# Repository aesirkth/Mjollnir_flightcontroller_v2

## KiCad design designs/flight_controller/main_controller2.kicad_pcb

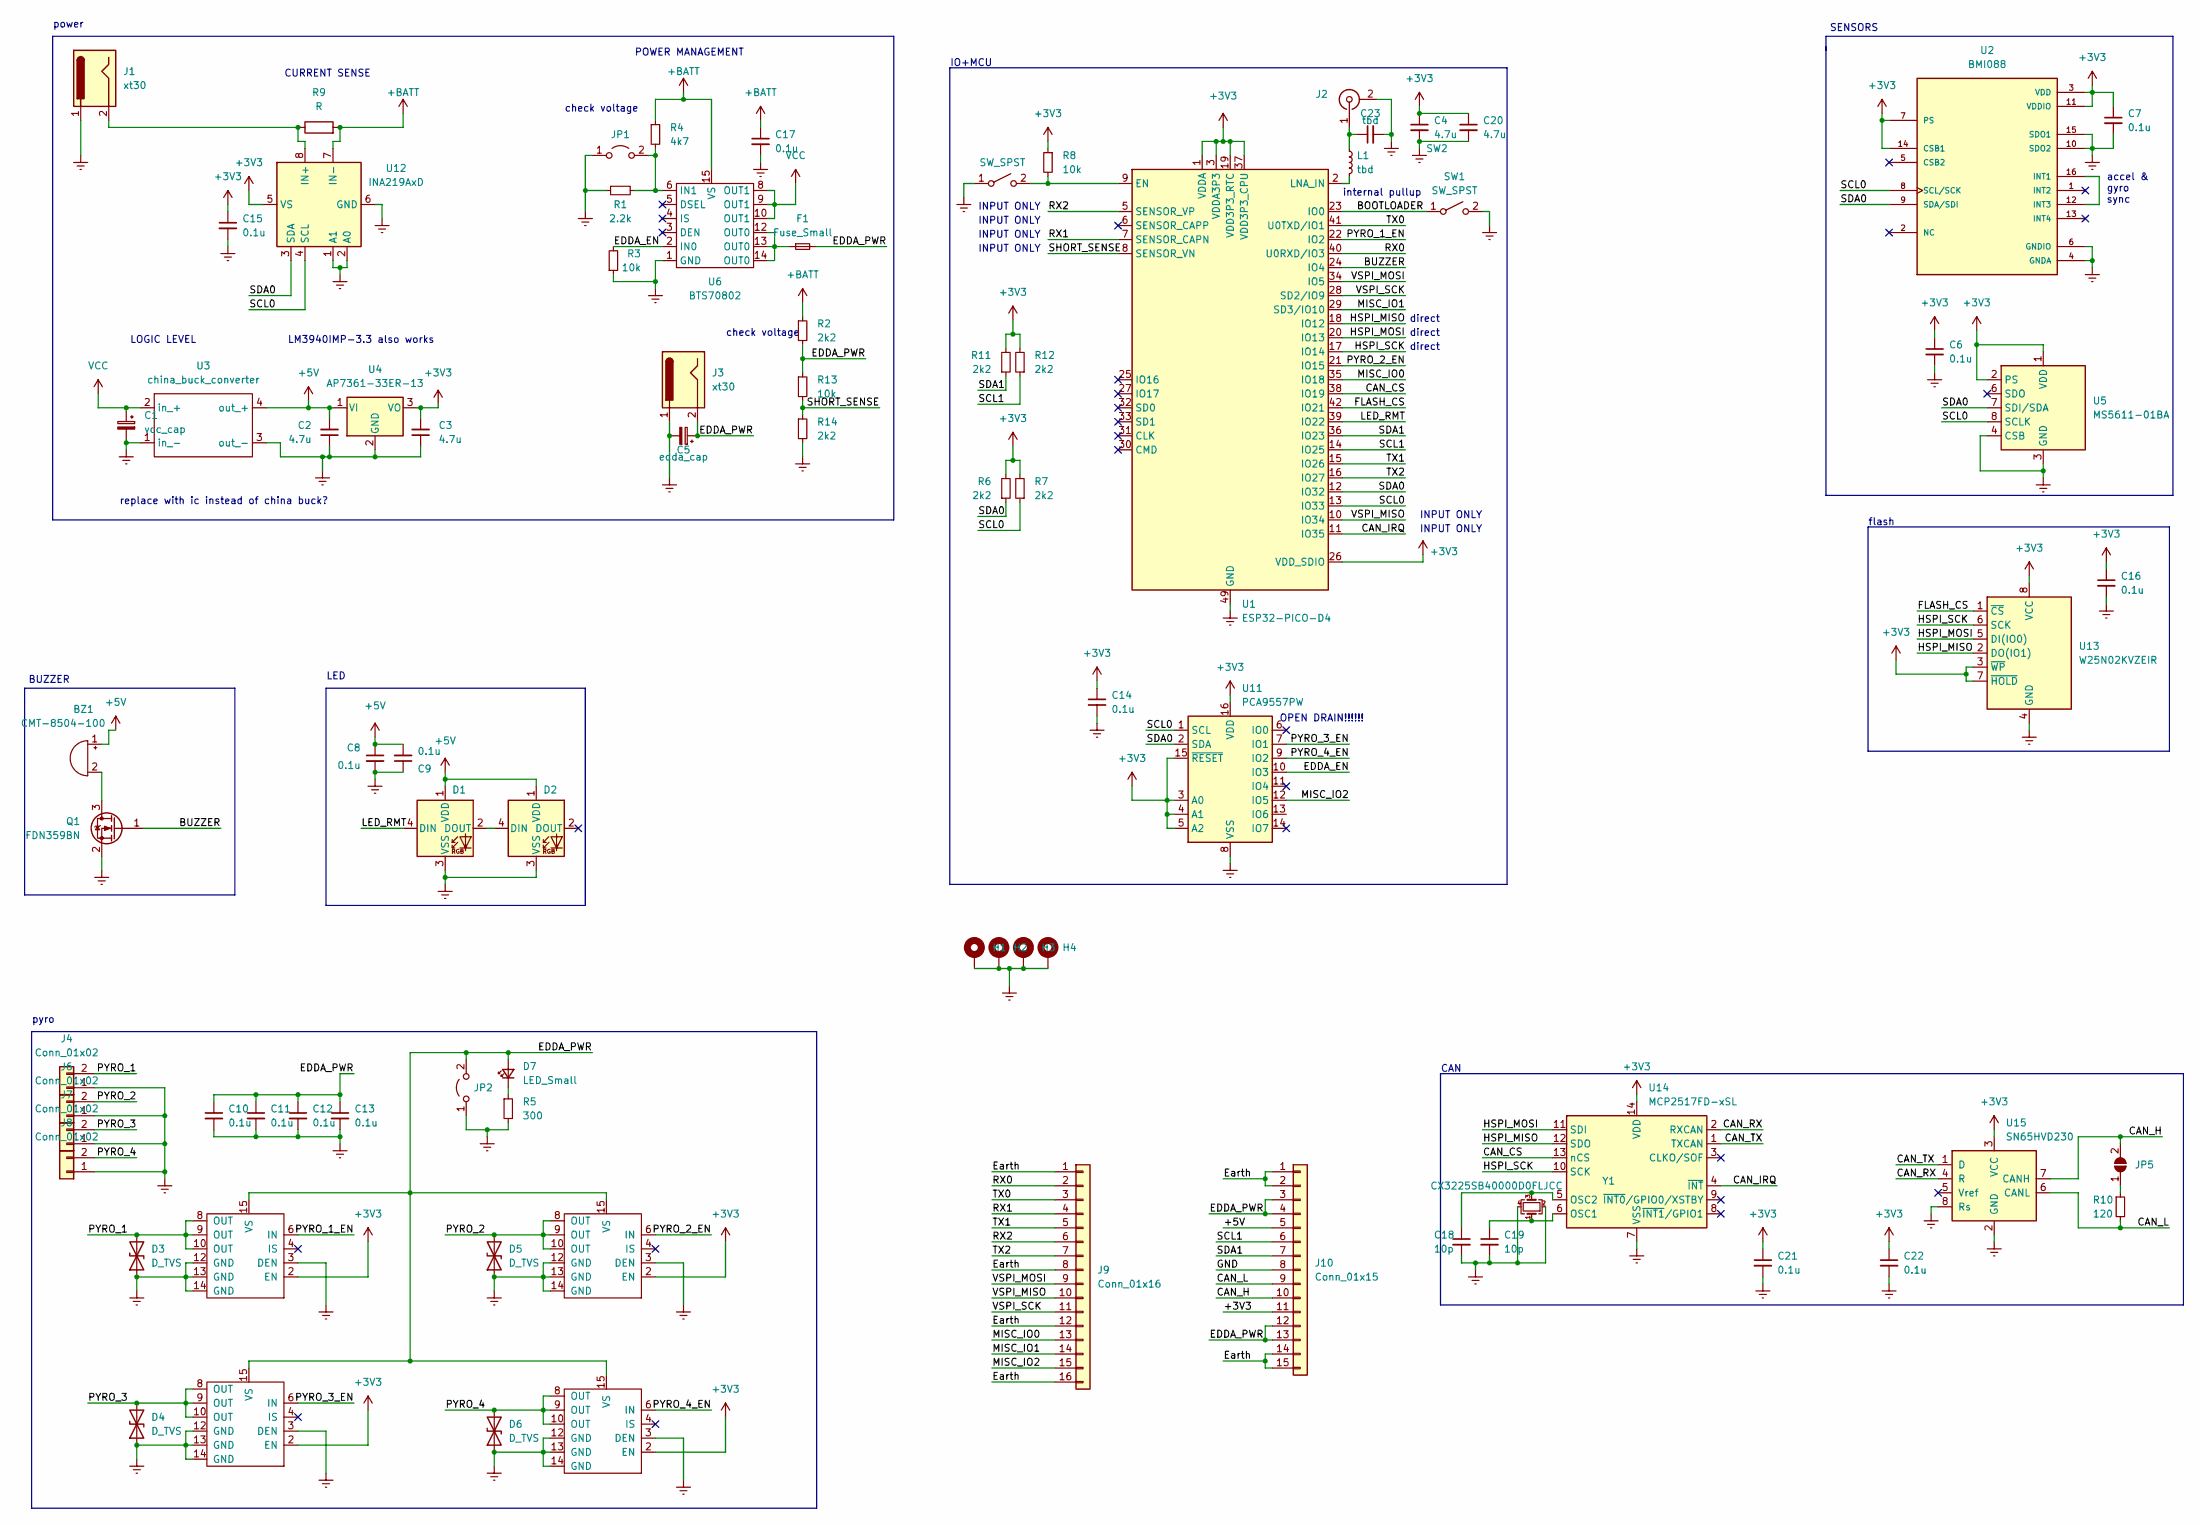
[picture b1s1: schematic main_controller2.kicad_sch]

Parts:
BZ1: CMT-8504-100; MagneticBuzzer_CUI_CMT-8504-100-SMT
C1: vcc_cap; CP_Radial_D5.0mm_P2.50mm
C2, C3, C4, C20: 4.7u; C_0603_1608Metric
C5: edda_cap; CP_Radial_D5.0mm_P2.50mm
C6, C7, C8, C9, C10, C11, C12, C13, C14, C15, C16, C17, C21, C22: 0.1u; C_0603_1608Metric
C18, C19: 10p; C_0603_1608Metric
C23: tbd; C_0603_1608Metric
D1, D2: WS2812B; LED_WS2812B_PLCC4_5.0x5.0mm_P3.2mm
D3, D4, D5, D6: D_TVS; D_0805_2012Metric
D7: LED_Small; D_0805_2012Metric
F1: Fuse_Small; Fuse_1812_4532Metric_Pad1.30x3.40mm_HandSolder
H1, H2, H3, H4: MountingHole_Pad; MountingHole_2.2mm_M2_Pad_Via
J1: xt30; AMASS_XT30PW-M_1x02_P2.50mm_Horizontal
J2: Conn_Coaxial; U.FL_Molex_MCRF_73412-0110_Vertical
J3: xt30; AMASS_XT30PW-F_1x02_P2.50mm_Horizontal
J4, J6, J7, J8: Conn_01x02; JST_XH_S2B-XH-A_1x02_P2.50mm_Horizontal
J9: Conn_01x16; PinHeader_1x16_P2.54mm_Vertical
J10: Conn_01x15; PinHeader_1x15_P2.54mm_Vertical
JP1: power switch; JST_XH_S2B-XH-A_1x02_P2.50mm_Horizontal
JP2: pyro_arm; AMASS_XT30PW-F_1x02_P2.50mm_Horizontal
JP5: SolderJumper_2_Open; SolderJumper-2_P1.3mm_Open_TrianglePad1.0x1.5mm
L1: tbd; L_0603_1608Metric
Q1: FDN359BN; SOT-23
R1: 2.2k; R_0603_1608Metric
R2, R6, R7, R11, R12, R14: 2k2; R_0603_1608Metric
R3, R8, R13: 10k; R_0603_1608Metric
R4: 4k7; R_0603_1608Metric
R5: 300; R_0603_1608Metric
R9: R; R_1206_3216Metric_Pad1.30x1.75mm_HandSolder
R10: 120; R_0603_1608Metric
SW1, SW2: SW_SPST; PinHeader_1x02_P1.27mm_Vertical
U1: ESP32-PICO-D4; QFN-48-1EP_7x7mm_P0.5mm_EP5.3x5.3mm
U2: BMI088; PQFN50P450X300X100-16N
U3: china_buck_converter; china_buck
U4: AP7361-33ER-13; SOT-223-3_TabPin2
U5: MS5611-01BA; LGA-8_3x5mm_P1.25mm
U6: BTS70802; Infineon_PG-TSDSO-14-22
U7, U8, U9, U10: BTN7030-1EPA; Infineon_PG-TSDSO-14-22
U11: PCA9557PW; TSSOP-16_4.4x5mm_P0.65mm
U12: INA219AxD; SOIC-8_3.9x4.9mm_P1.27mm
U13: W25N02KVZEIR; SON127P800X600X80-9N-D
U14: MCP2517FD-xSL; SOIC-14_3.9x8.7mm_P1.27mm
U15: SN65HVD230; SOIC-8_3.9x4.9mm_P1.27mm
Y1: CX3225SB40000D0FLJCC

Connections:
+3V3: C3.2, C4.1, C6.1, C7.1, C14.1, C15.1, C16.1, C20.1, C21.1, C22.1, J10.11, R6.2, R7.2, R8.1, R11.2, R12.2, U1.1 (VDDA), U1.3 (VDDA3P3), U1.4 (VDDA3P3), U1.19 (VDD3P3_RTC), U1.26 (VDD_SDIO), U1.37 (VDD3P3_CPU), U1.43 (VDDA), U1.46 (VDDA), U2.3 (VDD), U2.7 (PS), U2.11 (VDDIO), U2.14 (CSB1), U4.3 (VO), U5.1 (VDD), U5.2 (PS), U7.2 (EN), U8.2 (EN), U9.2 (EN), U10.2 (EN), U11.3 (A0), U11.4 (A1), U11.5 (A2), U11.15 (~RESET), U11.16 (VDD), U12.5 (VS), U13.3 (~WP), U13.7 (~HOLD), U13.8 (VCC), U14.14 (VDD), U15.3 (VCC)
+5V: BZ1.1 (-), C2.2, C8.1, C9.2, D1.1 (VDD), D2.1 (VDD), J10.5, U3.4 (out_+), U4.1 (VI)
+BATT: C17.1, R2.1, R4.1, R9.2, U6.15 (VS), U12.7 (IN-)
/BOOTLOADER: SW1.1 (A), U1.23 (IO0)
/BUZZER: Q1.1 (G), U1.24 (IO4)
/CAN_CS: U1.38 (IO19), U14.13 (nCS)
/CAN_H: J10.10, JP5.2 (B), U15.7 (CANH)
/CAN_IRQ: U1.11 (IO35), U14.4 (~INT)
/CAN_L: J10.9, R10.2, U15.6 (CANL)
/CAN_RX: U14.2 (RXCAN), U15.4 (R)
/CAN_TX: U14.1 (TXCAN), U15.1 (D)
/EDDA_EN: R3.2, U6.2 (IN0), U11.10 (IO3)
/EDDA_PWR: C5.1, C10.1, C11.1, C12.1, C13.1, D7.2 (A), F1.2, J3.2, J10.3, J10.4, J10.12, J10.13, JP2.2 (B), R2.2, R13.1, U7.15 (VS), U8.15 (VS), U9.15 (VS), U10.15 (VS)
/FLASH_CS: U1.42 (IO21), U13.1 (~CS)
/GND: J10.8
/HSPI_MISO: U1.18 (IO12), U13.2 (DO(IO1)), U14.12 (SDO)
/HSPI_MOSI: U1.20 (IO13), U13.5 (DI(IO0)), U14.11 (SDI)
/HSPI_SCK: U1.17 (IO14), U13.6 (SCK), U14.10 (SCK)
/LED_RMT: D1.4 (DIN), U1.39 (IO22)
/MISC_IO0: J9.13, U1.35 (IO18)
/MISC_IO1: J9.14, U1.29 (SD3/IO10)
/MISC_IO2: J9.15, U11.12 (IO5)
/PYRO_1: D3.2 (A2), J4.2, U7.8 (OUT), U7.9 (OUT), U7.10 (OUT)
/PYRO_1_EN: U1.22 (IO2), U7.6 (IN)
/PYRO_2: D5.2 (A2), J6.2, U9.8 (OUT), U9.9 (OUT), U9.10 (OUT)
/PYRO_2_EN: U1.21 (IO15), U9.6 (IN)
/PYRO_3: D4.2 (A2), J7.2, U8.8 (OUT), U8.9 (OUT), U8.10 (OUT)
/PYRO_3_EN: U8.6 (IN), U11.7 (IO1)
/PYRO_4: D6.2 (A2), J8.2, U10.8 (OUT), U10.9 (OUT), U10.10 (OUT)
/PYRO_4_EN: U10.6 (IN), U11.9 (IO2)
/RX0: J9.2, U1.40 (U0RXD/IO3)
/RX1: J9.4, U1.7 (SENSOR_CAPN)
/RX2: J9.6, U1.5 (SENSOR_VP)
/SCL0: R7.1, U1.13 (IO33), U2.8 (SCL/SCK), U5.8 (SCLK), U11.1 (SCL), U12.4 (SCL)
/SCL1: J10.6, R12.1, U1.14 (IO25)
/SDA0: R6.1, U1.12 (IO32), U2.9 (SDA/SDI), U5.7 (SDI/SDA), U11.2 (SDA), U12.3 (SDA)
/SDA1: J10.7, R11.1, U1.36 (IO23)
/SHORT_SENSE: R13.2, R14.1, U1.8 (SENSOR_VN)
/TX0: J9.3, U1.41 (U0TXD/IO1)
/TX1: J9.5, U1.15 (IO26)
/TX2: J9.7, U1.16 (IO27)
/VSPI_MISO: J9.10, U1.10 (IO34)
/VSPI_MOSI: J9.9, U1.34 (IO5)
/VSPI_SCK: J9.11, U1.28 (SD2/IO9)
Earth: C1.2, C2.1, C3.1, C4.2, C5.2, C6.2, C7.2, C8.2, C9.1, C10.2, C11.2, C12.2, C13.2, C14.2, C15.2, C16.2, C17.2, C18.2, C19.2, C20.2, C21.2, C22.2, C23.2, D1.3 (VSS), D2.3 (VSS), D3.1 (A1), D4.1 (A1), D5.1 (A1), D6.1 (A1), H1.1, H2.1, H3.1, H4.1, J1.1, J2.2 (Ext), J3.1, J4.1, J6.1, J7.1, J8.1, J9.1, J9.8, J9.12, J9.16, J10.1, J10.2, J10.14, J10.15, JP1.1 (A), JP2.1 (A), Q1.2 (S), R1.1, R3.1, R5.2, R14.2, SW1.2 (B), SW2.1 (A), U1.49 (GND), U2.4 (GNDA), U2.6 (GNDIO), U2.10 (SDO2), U2.15 (SDO1), U3.1 (in_-), U3.3 (out_-), U4.2 (GND), U5.3 (GND), U5.4 (CSB), U5.5 (CSB), U6.1 (GND), U7.3 (DEN), U7.12 (GND), U7.13 (GND), U7.14 (GND), U8.3 (DEN), U8.12 (GND), U8.13 (GND), U8.14 (GND), U9.3 (DEN), U9.12 (GND), U9.13 (GND), U9.14 (GND), U10.3 (DEN), U10.12 (GND), U10.13 (GND), U10.14 (GND), U11.8 (VSS), U12.1 (A1), U12.2 (A0), U12.6 (GND), U13.4 (GND), U14.7 (VSS), U15.2 (GND), U15.8 (Rs), Y1.2, Y1.4
unnamed: BZ1.2 (+), Q1.3 (D)
unnamed: C18.1, U14.5 (OSC2), Y1.3
unnamed: C19.1, U14.6 (OSC1), Y1.1
unnamed: C23.1, J2.1 (In), L1.1
unnamed: D1.2 (DOUT), D2.4 (DIN)
unnamed: D7.1 (K), R5.1
unnamed: F1.1, U6.12 (OUT0), U6.13 (OUT0), U6.14 (OUT0)
unnamed: J1.2, R9.1, U12.8 (IN+)
unnamed: JP1.2 (B), R1.2, R4.2, U6.6 (IN1)
unnamed: JP5.1 (A), R10.1
unnamed: L1.2, U1.2 (LNA_IN)
unnamed: R8.2, SW2.2 (B), U1.9 (EN)
unnamed: U2.12 (INT3), U2.16 (INT1)
VCC: C1.1, U3.2 (in_+), U6.8 (OUT1), U6.9 (OUT1), U6.10 (OUT1)

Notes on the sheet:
replace with ic instead of china buck?
direct
INPUT ONLY
IO+MCU
pyro
CURRENT SENSE
check voltage
BUZZER
flash
LOGIC LEVEL
LM3940IMP-3.3 also works
CAN
internal pullup
POWER MANAGEMENT
accel & gyro sync
LED
SENSORS
OPEN DRAIN!!!!!!
power

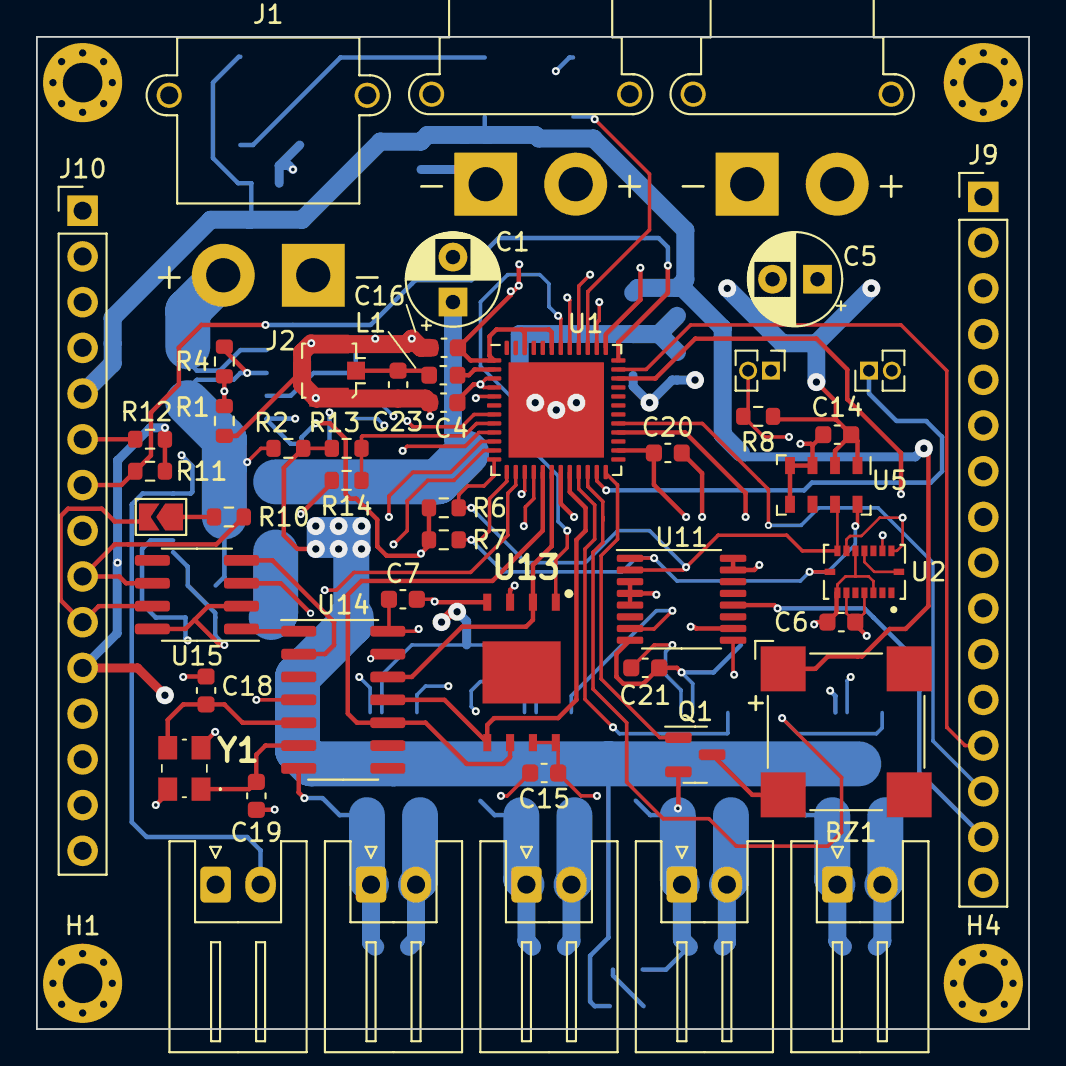
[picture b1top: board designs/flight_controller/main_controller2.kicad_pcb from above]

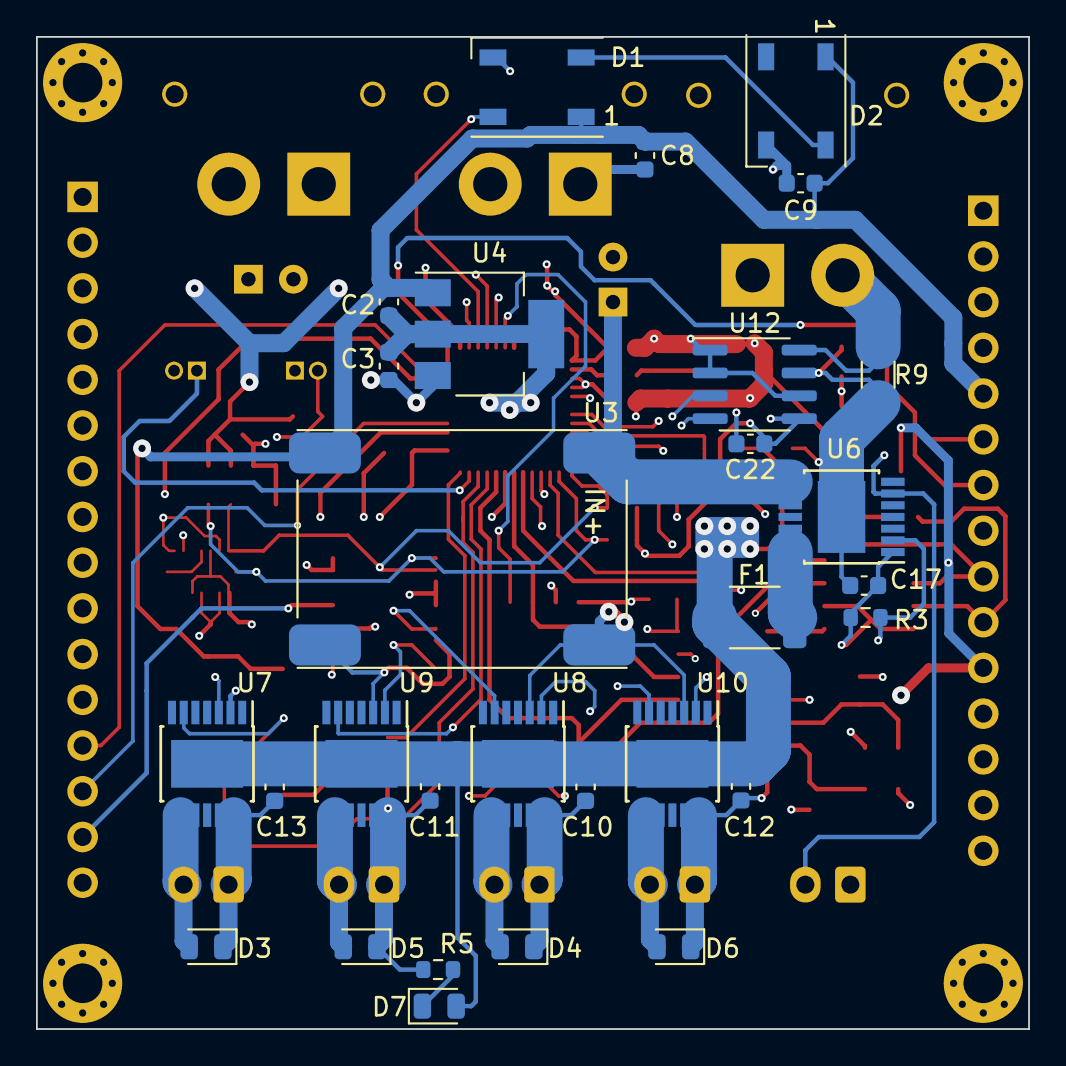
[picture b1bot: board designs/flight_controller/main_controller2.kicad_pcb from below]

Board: 4 copper layers, 55.1 x 55.1 mm, 82 parts (29 on the bottom side), 58 nets.

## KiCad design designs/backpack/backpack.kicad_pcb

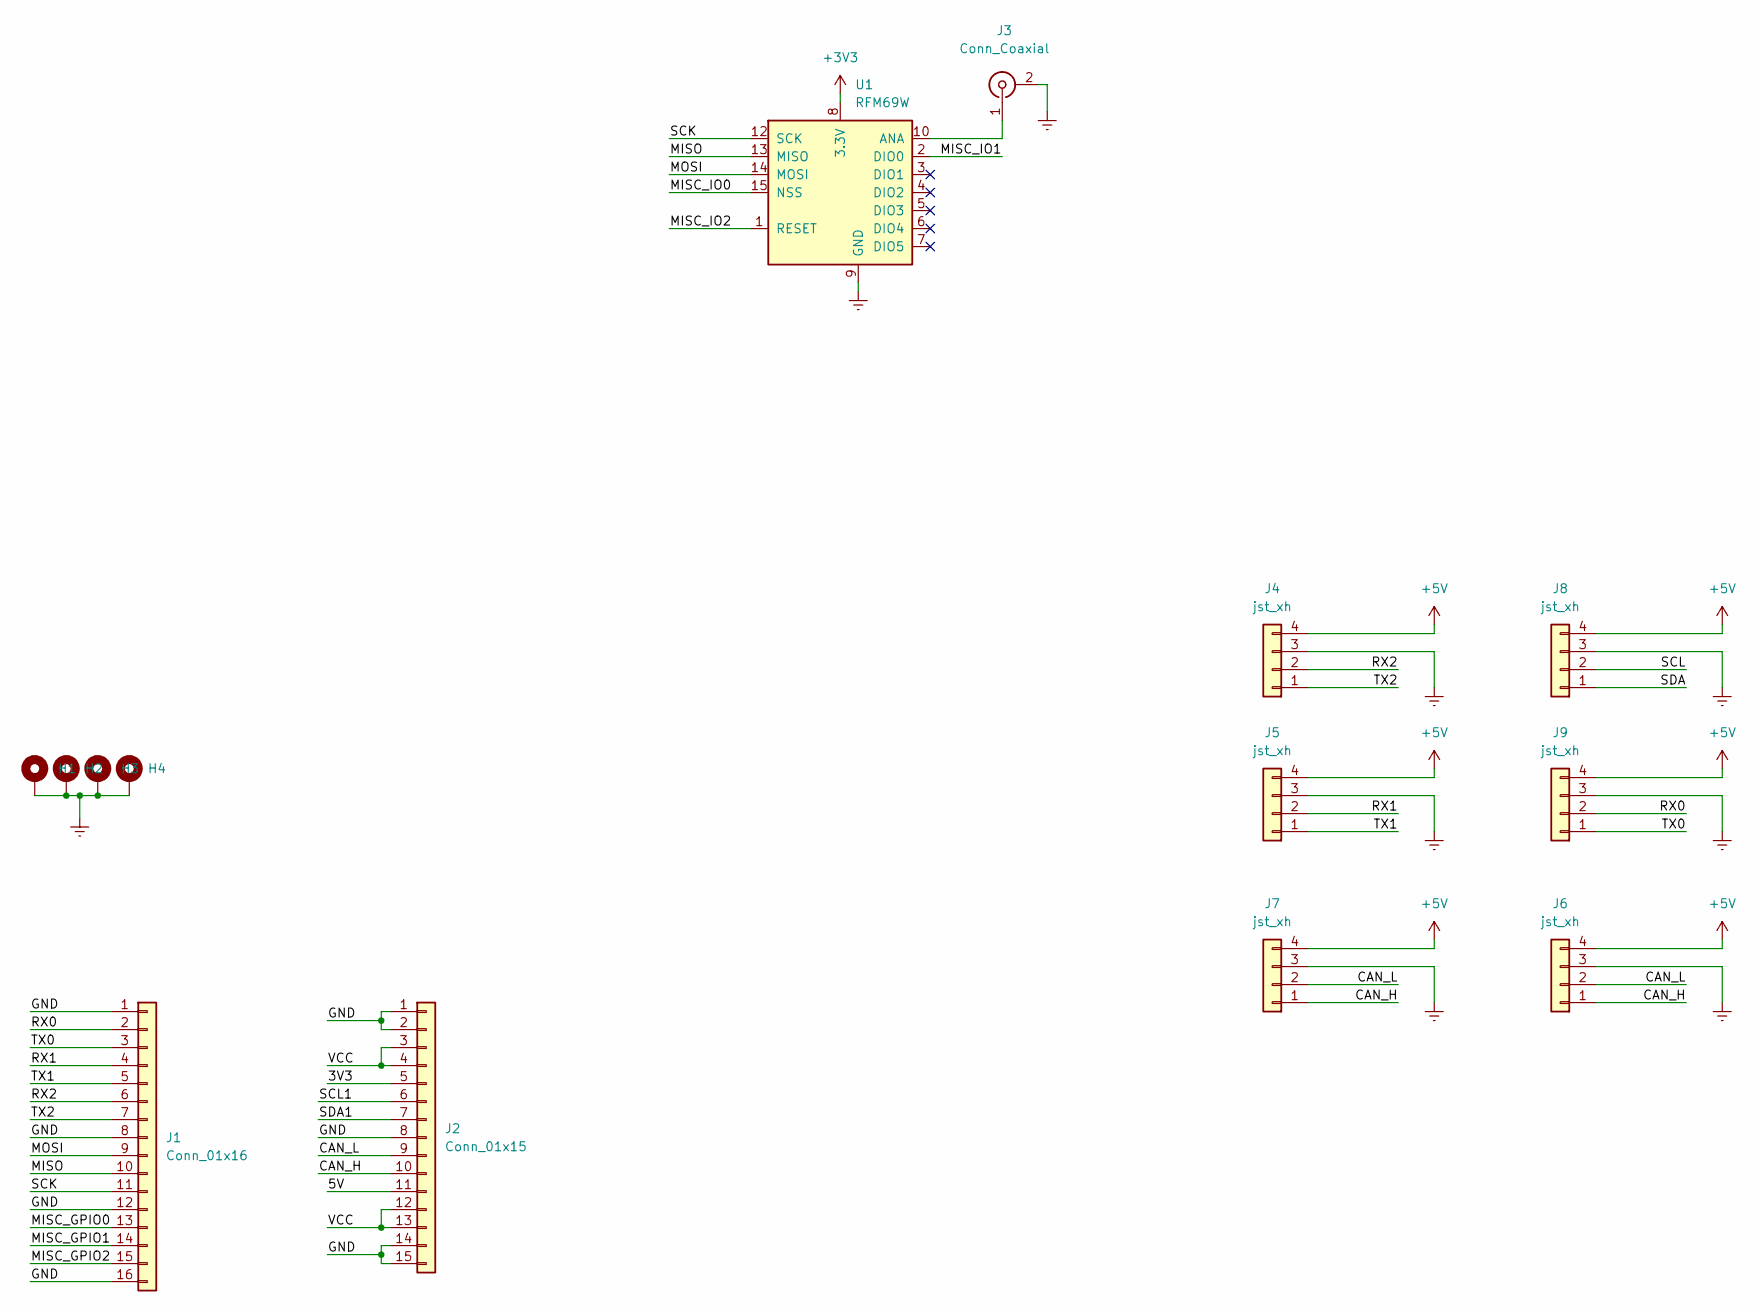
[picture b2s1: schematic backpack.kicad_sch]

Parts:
H1, H2, H3, H4: MountingHole_Pad; MountingHole_2.2mm_M2_Pad_Via
J1: Conn_01x16; PinHeader_1x16_P2.54mm_Vertical
J2: Conn_01x15; PinHeader_1x15_P2.54mm_Vertical
J3: Conn_Coaxial; SMA_Molex_73251-1153_EdgeMount_Horizontal
J4, J5, J6, J7, J8, J9: jst_xh; JST_XH_B4B-XH-A_1x04_P2.50mm_Vertical
U1: RFM69W; HOPERF_RFM69HW

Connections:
+3V3: U1.8 (3.3V)
+5V: J4.4, J5.4, J6.4, J7.4, J8.4, J9.4
/3V3: J2.5
/5V: J2.11
/CAN_H: J2.10, J6.1, J7.1
/CAN_L: J2.9, J6.2, J7.2
/GND: J1.1, J1.8, J1.12, J1.16, J2.1, J2.2, J2.8, J2.14, J2.15
/MISC_GPIO0: J1.13
/MISC_GPIO1: J1.14
/MISC_GPIO2: J1.15
/MISC_IO0: U1.15 (NSS)
/MISC_IO1: U1.2 (DIO0)
/MISC_IO2: U1.1 (RESET)
/MISO: J1.10, U1.13 (MISO)
/MOSI: J1.9, U1.14 (MOSI)
/RX0: J1.2, J9.2
/RX1: J1.4, J5.2
/RX2: J1.6, J4.2
/SCK: J1.11, U1.12 (SCK)
/SCL: J8.2
/SCL1: J2.6
/SDA: J8.1
/SDA1: J2.7
/TX0: J1.3, J9.1
/TX1: J1.5, J5.1
/TX2: J1.7, J4.1
/VCC: J2.3, J2.4, J2.12, J2.13
Earth: H1.1, H2.1, H3.1, H4.1, J3.2 (Ext), J4.3, J5.3, J6.3, J7.3, J8.3, J9.3, U1.9 (GND), U1.11 (GND)
unnamed: J3.1 (In), U1.10 (ANA)

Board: 4 copper layers, 14 parts (0 on the bottom side), 16 nets, no tracks yet.

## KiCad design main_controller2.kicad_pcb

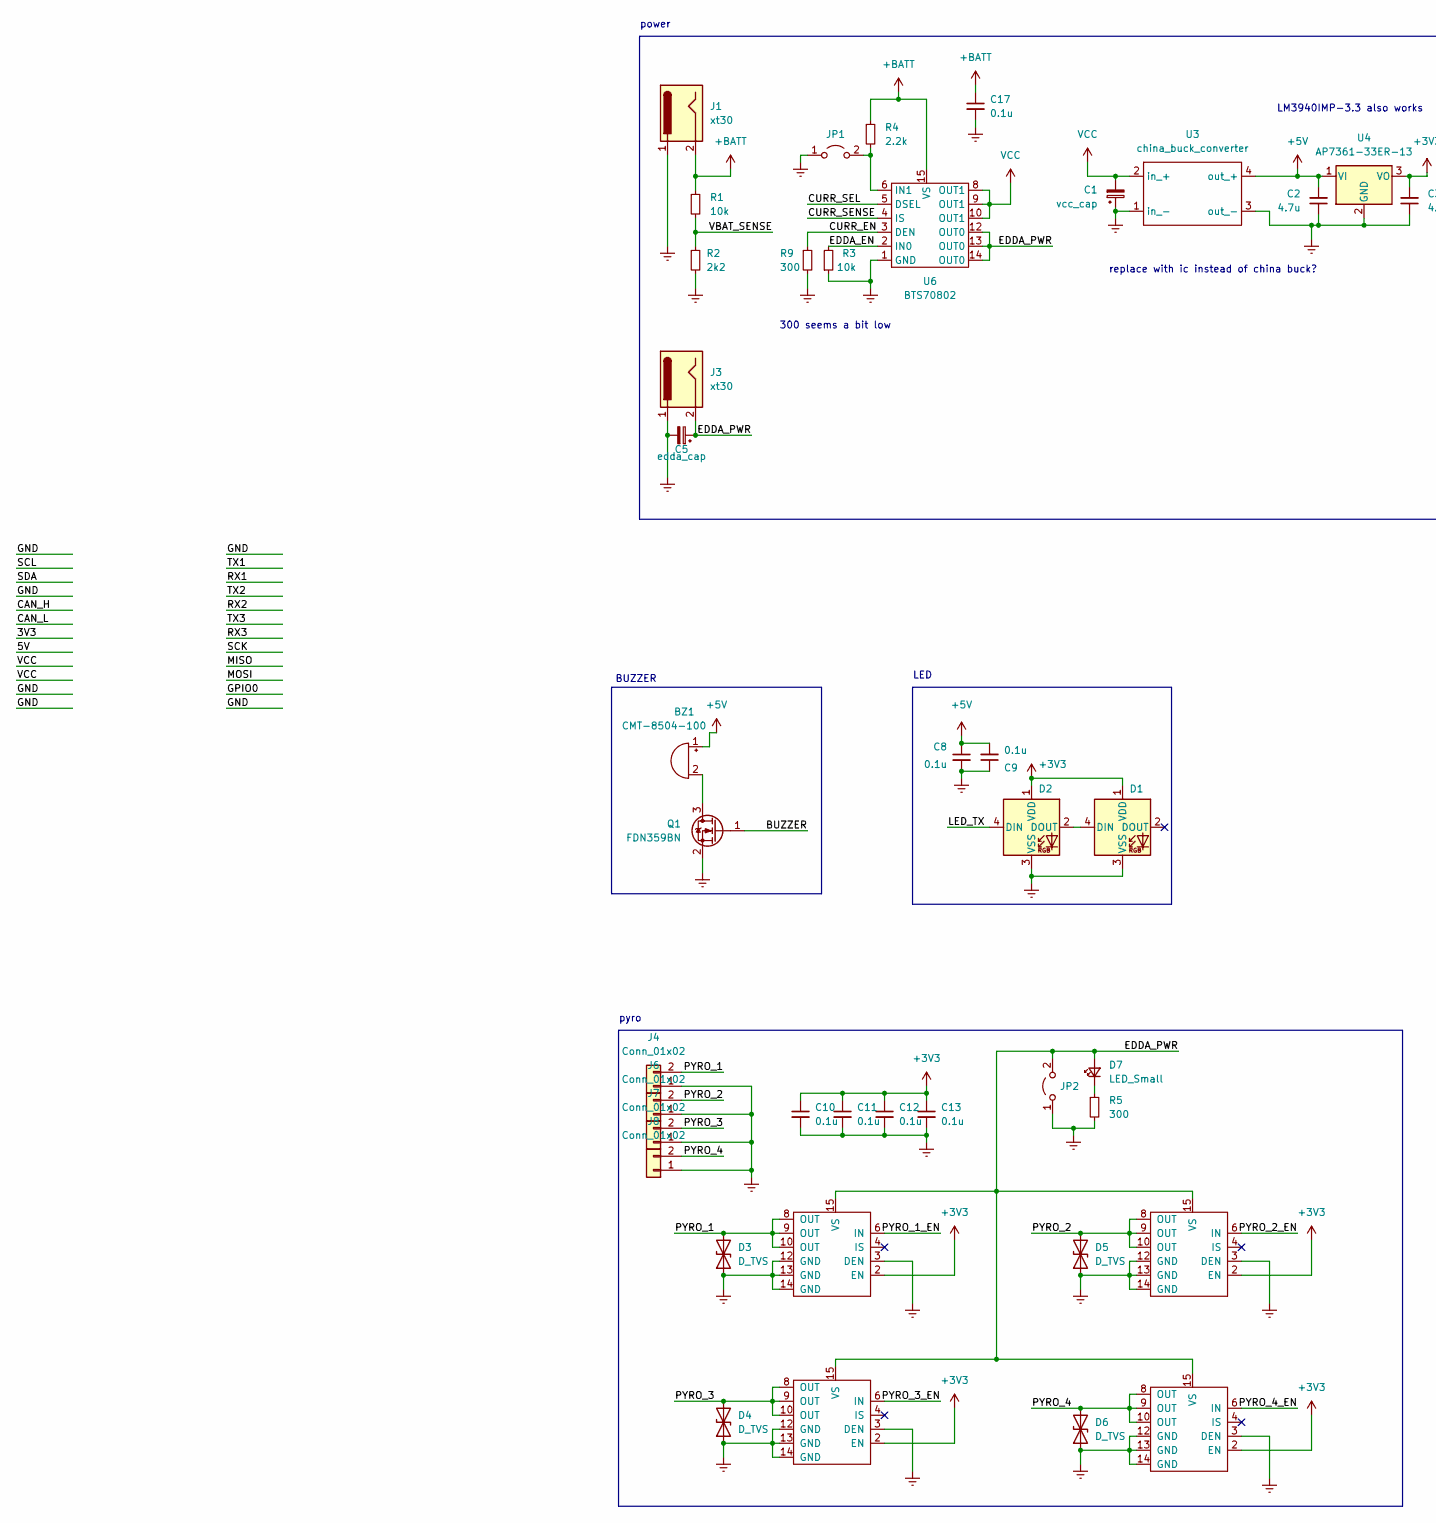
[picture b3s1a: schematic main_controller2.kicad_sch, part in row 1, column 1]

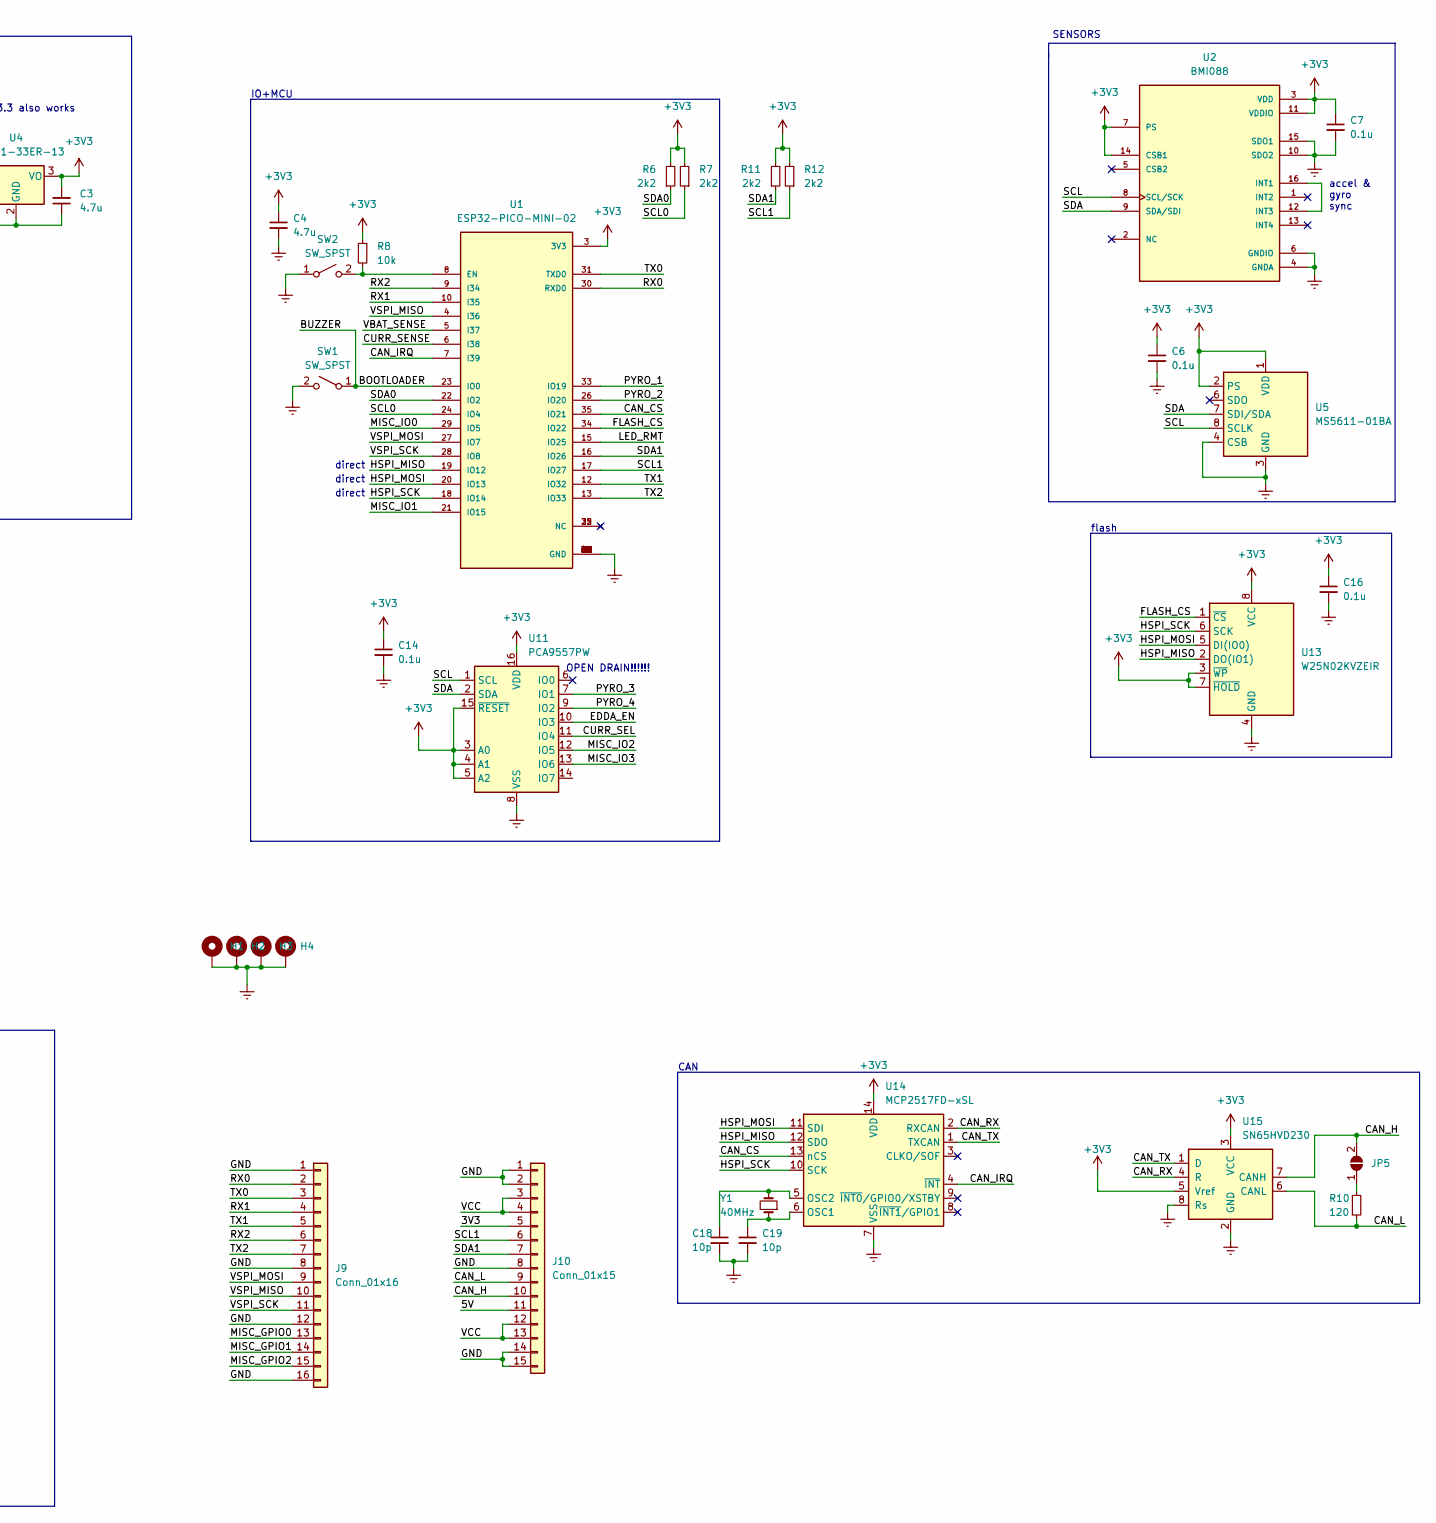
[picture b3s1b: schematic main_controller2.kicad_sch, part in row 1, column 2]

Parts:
BZ1: CMT-8504-100; MagneticBuzzer_CUI_CMT-8504-100-SMT
C1: vcc_cap; CP_Radial_D5.0mm_P2.50mm
C2, C3, C4: 4.7u; C_0603_1608Metric
C5: edda_cap; CP_Radial_D5.0mm_P2.50mm
C6, C7, C8, C9, C10, C11, C12, C13, C14, C16, C17: 0.1u; C_0603_1608Metric
C18, C19: 10p; C_0603_1608Metric
D1, D2: WS2812B; LED_WS2812B-2020_PLCC4_2.0x2.0mm
D3, D4, D5, D6: D_TVS; D_0805_2012Metric
D7: LED_Small; D_0805_2012Metric
H1, H2, H3, H4: MountingHole_Pad; MountingHole_2.2mm_M2_Pad_Via
J1: xt30; AMASS_XT30PW-M_1x02_P2.50mm_Horizontal
J3: xt30; AMASS_XT30PW-F_1x02_P2.50mm_Horizontal
J4, J6, J7, J8: Conn_01x02; JST_XH_S2B-XH-A_1x02_P2.50mm_Horizontal
J9: Conn_01x16; PinHeader_1x16_P2.54mm_Vertical
J10: Conn_01x15; PinHeader_1x15_P2.54mm_Vertical
JP1: power switch; JST_XH_S2B-XH-A_1x02_P2.50mm_Horizontal
JP2: pyro_arm; AMASS_XT30PW-F_1x02_P2.50mm_Horizontal
JP5: SolderJumper_2_Open; SolderJumper-2_P1.3mm_Open_TrianglePad1.0x1.5mm
Q1: FDN359BN; SOT-23
R1, R3, R8: 10k; R_0603_1608Metric
R2, R6, R7, R11, R12: 2k2; R_0603_1608Metric
R4: 2.2k; R_0603_1608Metric
R5, R9: 300; R_0603_1608Metric
R10: 120; R_0603_1608Metric
SW1, SW2: SW_SPST; PinHeader_1x02_P1.27mm_Vertical
U1: ESP32-PICO-MINI-02; MODULE_ESP32-PICO-MINI-02U; PARTREV v1.0
U2: BMI088; PQFN50P450X300X100-16N
U3: china_buck_converter; china_buck
U4: AP7361-33ER-13; SOT-223-3_TabPin2
U5: MS5611-01BA; LGA-8_3x5mm_P1.25mm
U6: BTS70802; Infineon_PG-TSDSO-14-22
U7, U8, U9, U10: BTN7030-1EPA; Infineon_PG-TSDSO-14-22
U11: PCA9557PW; TSSOP-16_4.4x5mm_P0.65mm
U13: W25N02KVZEIR; SON127P800X600X80-9N-D
U14: MCP2517FD-xSL; SOIC-14_3.9x8.7mm_P1.27mm
U15: SN65HVD230; SOIC-8_3.9x4.9mm_P1.27mm
Y1: 40MHz; Oscillator_SMD_SeikoEpson_SG8002CE-4Pin_3.2x2.5mm_HandSolde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

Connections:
+3V3: C3.2, C4.1, C6.1, C7.1, C10.1, C11.1, C12.1, C13.1, C14.1, C16.1, D1.1 (VDD), D2.1 (VDD), R6.2, R7.2, R8.1, R11.2, R12.2, U1.3 (3V3), U2.3 (VDD), U2.7 (PS), U2.11 (VDDIO), U2.14 (CSB1), U4.3 (VO), U5.1 (VDD), U5.2 (PS), U7.2 (EN), U8.2 (EN), U9.2 (EN), U10.2 (EN), U11.3 (A0), U11.4 (A1), U11.5 (A2), U11.15 (~RESET), U11.16 (VDD), U13.3 (~WP), U13.7 (~HOLD), U13.8 (VCC), U14.14 (VDD), U15.3 (VCC), U15.5 (Vref)
+5V: BZ1.1 (-), C2.2, C8.1, C9.2, U3.4 (out_+), U4.1 (VI)
+BATT: C17.1, J1.2, R1.1, R4.1, U6.15 (VS)
/3V3: J10.5
/5V: J10.11
/BOOTLOADER: Q1.1 (G), SW1.1 (A), U1.23 (IO0)
/CAN_CS: U1.35 (IO21), U14.13 (nCS)
/CAN_H: J10.10, JP5.2 (B), U15.7 (CANH)
/CAN_IRQ: U1.7 (I39), U14.4 (~INT)
/CAN_L: J10.9, R10.2, U15.6 (CANL)
/CAN_RX: U14.2 (RXCAN), U15.4 (R)
/CAN_TX: U14.1 (TXCAN), U15.1 (D)
/CURR_EN: R9.1, U6.3 (DEN)
/CURR_SEL: U6.5 (DSEL), U11.11 (IO4)
/CURR_SENSE: U1.6 (I38), U6.4 (IS)
/EDDA_EN: R3.2, U6.2 (IN0), U11.10 (IO3)
/EDDA_PWR: C5.1, D7.2 (A), J3.2, JP2.2 (B), U6.12 (OUT0), U6.13 (OUT0), U6.14 (OUT0), U7.15 (VS), U8.15 (VS), U9.15 (VS), U10.15 (VS)
/FLASH_CS: U1.34 (IO22), U13.1 (~CS)
/GND: J9.1, J9.8, J9.12, J9.16, J10.1, J10.2, J10.8, J10.14, J10.15
/HSPI_MISO: U1.19 (IO12), U13.2 (DO(IO1)), U14.12 (SDO)
/HSPI_MOSI: U1.20 (IO13), U13.5 (DI(IO0)), U14.11 (SDI)
/HSPI_SCK: U1.18 (IO14), U13.6 (SCK), U14.10 (SCK)
/LED_RMT: U1.15 (IO25)
/LED_TX: D2.4 (DIN)
/MISC_GPIO0: J9.13
/MISC_GPIO1: J9.14
/MISC_GPIO2: J9.15
/MISC_IO0: U1.29 (IO5)
/MISC_IO1: U1.21 (IO15)
/MISC_IO2: U11.12 (IO5)
/MISC_IO3: U11.13 (IO6)
/PYRO_1: D3.2 (A2), J4.2, U1.33 (IO19), U7.8 (OUT), U7.9 (OUT), U7.10 (OUT)
/PYRO_1_EN: U7.6 (IN)
/PYRO_2: D5.2 (A2), J6.2, U1.26 (IO20), U9.8 (OUT), U9.9 (OUT), U9.10 (OUT)
/PYRO_2_EN: U9.6 (IN)
/PYRO_3: D4.2 (A2), J7.2, U8.8 (OUT), U8.9 (OUT), U8.10 (OUT), U11.7 (IO1)
/PYRO_3_EN: U8.6 (IN)
/PYRO_4: D6.2 (A2), J8.2, U10.8 (OUT), U10.9 (OUT), U10.10 (OUT), U11.9 (IO2)
/PYRO_4_EN: U10.6 (IN)
/RX0: J9.2, U1.30 (RXD0)
/RX1: J9.4, U1.10 (I35)
/RX2: J9.6, U1.9 (I34)
/SCL: U2.8 (SCL/SCK), U5.8 (SCLK), U11.1 (SCL)
/SCL0: R7.1, U1.24 (IO4)
/SCL1: J10.6, R12.1, U1.17 (IO27)
/SDA: U2.9 (SDA/SDI), U5.7 (SDI/SDA), U11.2 (SDA)
/SDA0: R6.1, U1.22 (IO2)
/SDA1: J10.7, R11.1, U1.16 (IO26)
/TX0: J9.3, U1.31 (TXD0)
/TX1: J9.5, U1.12 (IO32)
/TX2: J9.7, U1.13 (IO33)
/VBAT_SENSE: R1.2, R2.1, U1.5 (I37)
/VSPI_MISO: J9.10, U1.4 (I36)
/VSPI_MOSI: J9.9, U1.27 (IO7)
/VSPI_SCK: J9.11, U1.28 (IO8)
Earth: C1.1, C2.1, C3.1, C4.2, C5.2, C6.2, C7.2, C8.2, C9.1, C10.2, C11.2, C12.2, C13.2, C14.2, C16.2, C17.2, C18.2, C19.2, D1.3 (VSS), D2.3 (VSS), D3.1 (A1), D4.1 (A1), D5.1 (A1), D6.1 (A1), H1.1, H2.1, H3.1, H4.1, J1.1, J3.1, J4.1, J6.1, J7.1, J8.1, JP1.1 (A), JP2.1 (A), Q1.2 (S), R2.2, R3.1, R5.2, R9.2, SW1.2 (B), SW2.1 (A), U1.1 (GND), U1.2 (GND), U1.11 (GND), U1.14 (GND), U1.36 (GND), U1.37 (GND), U1.38 (GND), U1.39 (GND), U1.40 (GND), U1.41 (GND), U1.42 (GND), U1.43 (GND), U1.44 (GND), U1.45 (GND), U1.46 (GND), U1.47 (GND), U1.48 (GND), U1.49 (GND), U1.50 (GND), U1.51 (GND), U1.52 (GND), U1.53 (GND), U1.54 (GND), U1.55 (GND), U1.56 (GND), U1.57 (GND), U1.58 (GND), U1.59 (GND), U1.60 (GND), U1.61 (GND), U2.4 (GNDA), U2.6 (GNDIO), U2.10 (SDO2), U2.15 (SDO1), U3.1 (in_-), U3.3 (out_-), U4.2 (GND), U5.3 (GND), U5.4 (CSB), U5.5 (CSB), U6.1 (GND), U7.3 (DEN), U7.12 (GND), U7.13 (GND), U7.14 (GND), U8.3 (DEN), U8.12 (GND), U8.13 (GND), U8.14 (GND), U9.3 (DEN), U9.12 (GND), U9.13 (GND), U9.14 (GND), U10.3 (DEN), U10.12 (GND), U10.13 (GND), U10.14 (GND), U11.8 (VSS), U13.4 (GND), U14.7 (VSS), U15.2 (GND), U15.8 (Rs)
unnamed: BZ1.2 (+), Q1.3 (D)
unnamed: C18.1, U14.5 (OSC2), Y1.2
unnamed: C19.1, U14.6 (OSC1), Y1.1
unnamed: D1.4 (DIN), D2.2 (DOUT)
unnamed: D7.1 (K), R5.1
unnamed: JP1.2 (B), R4.2, U6.6 (IN1)
unnamed: JP5.1 (A), R10.1
unnamed: R8.2, SW2.2 (B), U1.8 (EN)
unnamed: U2.12 (INT3), U2.16 (INT1)
VCC: C1.2, J10.3, J10.4, J10.12, J10.13, U3.2 (in_+), U6.8 (OUT1), U6.9 (OUT1), U6.10 (OUT1)

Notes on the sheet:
replace with ic instead of china buck?
direct
IO+MCU
pyro
BUZZER
flash
LM3940IMP-3.3 also works
CAN
accel & gyro sync
300 seems a bit low
LED
SENSORS
OPEN DRAIN!!!!!!
power

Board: 4 copper layers, 71 parts (13 on the bottom side), 51 nets, no tracks yet.

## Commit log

2022-11-22 initial commit (the all in one board)
2022-11-29 stackable version
2023-01-19 move to esp pico
2023-01-19 better structure
2023-01-19 clean up
2023-01-23 Placing all components, far from finished, basic routing started
2023-01-24 fix grid
2023-01-24 preliminary layout
2023-01-25 add ufl
2023-01-31 WIP: backpack
2023-02-22 routing done
2023-04-16 final design
